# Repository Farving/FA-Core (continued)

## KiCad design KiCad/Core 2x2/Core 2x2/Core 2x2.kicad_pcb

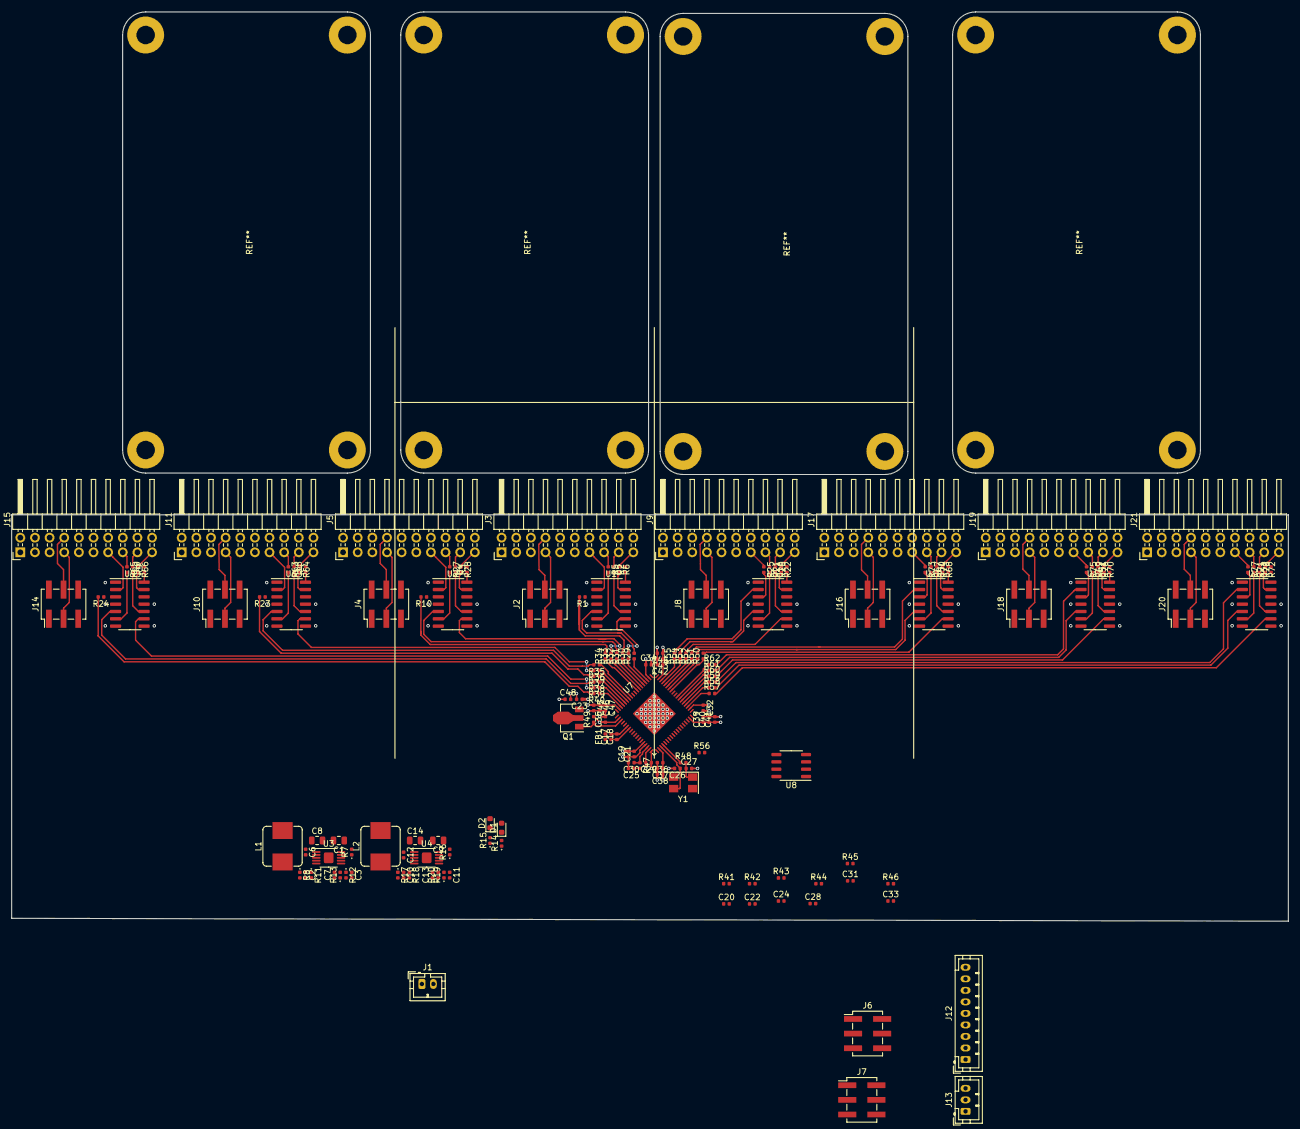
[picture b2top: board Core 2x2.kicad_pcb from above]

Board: 4 copper layers, 221.5 x 70.5 mm, 170 parts (0 on the bottom side), 181 nets.

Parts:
C1, C8, C9, C14: 10u; C_0805_2012Metric
C2, C10, C38, C41, C44, C47: 1u; C_0402_1005Metric
C3, C11, C36, C39, C42, C45: 10n; C_0402_1005Metric
C4, C5, C6, C12, C15, C16, C18, C21, C29, C32, C34, C35, C37, C40, C43, C46, C49, C50, C51, C52: 100n; C_0402_1005Metric
C7, C13: 10p; C_0402_1005Metric
C17, C19, C23, C48: 10u; C_0402_1005Metric
C20, C22, C24, C28, C31, C33: 100p; C_0402_1005Metric
C25: 5.6n; C_0402_1005Metric
C26, C27: 22p; C_0402_1005Metric
C30: 150p; C_0402_1005Metric
D1, D2: LED_Small; D_0603_1608Metric
FB1: 600Z; L_0402_1005Metric
J1: Conn_01x02_Female; JST_PH_B2B-PH-K_1x02_P2.00mm_Vertical
J2, J4, J6, J7, J8, J10, J14, J16, J18, J20: Conn_02x03_Odd_Even; PinHeader_2x03_P2.54mm_Vertical_SMD
J3, J5, J9, J11, J15, J17, J19, J21: 02x10; PinHeader_2x10_P2.54mm_Horizontal
J12: Conn_01x09_Male; JST_PH_B9B-PH-K_1x09_P2.00mm_Vertical
J13: Conn_01x03_Male; JST_PH_B3B-PH-K_1x03_P2.00mm_Vertical
L1, L2: 10u; L_Bourns_SRP7028A_7.3x6.6mm
Q1: 2STF2550; SOT-89-3
R1, R2, R3, R4, R5, R6, R9, R10, R21, R22, R23, R24, R25, R26, R27, R28, R29, R30, R31, R32, R33, R34, R35, R36, R37, R38, R39, R40, R50, R51, R52, R53, R54, R55, R56, R57, R58, R59, R60, R61, R62, R63, R64, R65, R66, R67, R68, R69, R70, R71, R72, R73, R74, R75, R76, R77, R78: 33R; R_0402_1005Metric
R7, R8, R16, R17: 0R; D_0402_1005Metric
R11, R18: 18k; D_0402_1005Metric
R12: 180k; D_0402_1005Metric
R13, R20: 1M; D_0402_1005Metric
R14, R15: 100R; D_0402_1005Metric
R19: 300k; D_0402_1005Metric
R41, R42, R43, R44, R45, R46, R48: 100R; R_0402_1005Metric
R47: 4.32k; R_0402_1005Metric
R49: 1k; R_0402_1005Metric
U1, U2, U5, U6, U9, U10, U11, U12: SN74AHC125; SOIC-14_3.9x8.7mm_P1.27mm
U3, U4: LT8608; MSOP-10-1EP_3x3mm_P0.5mm_EP1.68x1.88mm
U7: ADAU1452; LFCSP-72-1EP_10x10mm_P0.5mm_EP5.3x5.3mm
U8: M95M01; SO-8_3.9x4.9mm_P1.27mm
Y1: 12.288MHz; Crystal_SMD_5032-4Pin_5.0x3.2mm

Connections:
+3V3: C4.1, C5.1, C13.1, C14.1, C15.1, C16.1, C23.1, C29.1, C32.1, C34.1, C35.1, C49.1, C50.1, C51.1, C52.1, FB1.2, J3.1, J5.1, J9.1, J11.1, J15.1, J17.1, J19.1, J21.1, L2.2, Q1.3, R20.1, R49.2, U1.14, U2.14, U5.14, U6.14, U7.2, U7.18, U7.38, U7.56, U9.14, U10.14, U11.14, U12.14
+5V: C7.1, C8.1, C9.1, D1.2, D2.2, J3.2, J5.2, J9.2, J11.2, J15.2, J17.2, J19.2, J21.2, L1.2, R13.1, R16.1, U4.9
/DSP/AVDD: C17.1, C18.1, C19.1, C21.1, C25.2, C30.2, FB1.1, U7.7, U7.15
/DSP/BCLKI0: R29.2, U1.5
/DSP/BCLKI1: R32.2, U2.5
/DSP/BCLKI2: R35.2, U6.5
/DSP/BCLKI3: R38.2, U9.5
/DSP/BCLKO0: R58.2, U12.5
/DSP/BCLKO1: R61.2, U11.5
/DSP/BCLKO2: R51.2, U10.5
/DSP/BCLKO3: R54.2, U5.5
/DSP/DVDD: C36.1, C37.1, C38.1, C39.1, C40.1, C41.1, C42.1, C43.1, C44.1, C45.1, C46.1, C47.1, C48.1, Q1.2, U7.20, U7.35, U7.53, U7.71
/DSP/LRCLKI0: R30.2, U1.9
/DSP/LRCLKI1: R33.2, U2.9
/DSP/LRCLKI2: R36.2, U6.9
/DSP/LRCLKI3: R39.2, U9.9
/DSP/LRCLKO0: R57.2, U12.9
/DSP/LRCLKO1: R60.2, U11.9
/DSP/LRCLKO2: R50.2, U10.9
/DSP/LRCLKO3: R53.2, U5.9
/DSP/SDO0: R59.2, U12.2
/DSP/SDO1: R62.2, U11.2
/DSP/SDO2: R52.2, U10.2
/DSP/SDO3: R55.2, U5.2
/I2C_SCL: J2.1, J4.1, J8.1, J10.1, J13.2, J14.1, J16.1, J18.1, J20.1
/I2C_SDA: J2.2, J4.2, J8.2, J10.2, J13.3, J14.2, J16.2, J18.2, J20.2
/MCLK: R56.2, U1.12, U2.12, U5.12, U6.12, U9.12, U10.12, U11.12, U12.12
/MUTE: J3.6, J5.6, J9.6, J11.6, J15.6, J17.6, J19.6, J21.6
/PG_3V3: R15.1, U4.8
/PG_5V: R14.1, U3.8
/SDI0: R1.2, R31.2
/SDI1: R10.2, R34.2
/SDI2: R23.2, R37.2
/SDI3: R24.2, R40.2
/SHDN: J3.5, J5.5, J9.5, J11.5, J15.5, J17.5, J19.5, J21.5
/SPI_MISO: J3.9, J5.9, J9.9, J11.9, J12.3, J15.9, J17.9, J19.9, J21.9
/SPI_MOSI: J2.6, J4.6, J8.6, J10.6, J12.4, J14.6, J16.6, J18.6, J20.6
/SPI_SCK: J2.5, J4.5, J8.5, J10.5, J12.2, J14.5, J16.5, J18.5, J20.5
/SPI_SS3: J3.10, J5.10, J9.10, J11.10, J12.8, J15.10, J17.10, J19.10, J21.10
GND: C1.2, C2.2, C3.2, C4.2, C5.2, C8.2, C9.2, C10.2, C11.2, C14.2, C15.2, C16.2, C17.2, C18.2, C19.2, C20.2, C21.2, C22.2, C23.2, C24.2, C26.2, C27.2, C28.2, C29.2, C31.2, C32.2, C33.2, C34.2, C35.2, C36.2, C37.2, C38.2, C39.2, C40.2, C41.2, C42.2, C43.2, C44.2, C45.2, C46.2, C47.2, C48.2, C49.2, C50.2, C51.2, C52.2, J1.2, J3.3, J3.4, J3.14, J3.16, J3.18, J3.20, J5.3, J5.4, J5.14, J5.16, J5.18, J5.20, J9.3, J9.4, J9.14, J9.16, J9.18, J9.20, J11.3, J11.4, J11.14, J11.16, J11.18, J11.20, J12.1, J13.1, J15.3, J15.4, J15.14, J15.16, J15.18, J15.20, J17.3, J17.4, J17.14, J17.16, J17.18, J17.20, J19.3, J19.4, J19.14, J19.16, J19.18, J19.20, J21.3, J21.4, J21.14, J21.16, J21.18, J21.20, R11.2, R12.2, R18.2, R19.2, U1.1, U1.4, U1.7, U1.8, U1.11, U2.1, U2.4, U2.7, U2.8, U2.11, U3.11, U4.11, U5.1, U5.4, U5.7, U5.8, U5.11, U6.1, U6.4, U6.7, U6.8, U6.11, U7.1, U7.6, U7.14, U7.17, U7.19, U7.25, U7.36, U7.37, U7.54, U7.55, U7.72, U7.73, U8.4, U9.1, U9.4, U9.7, U9.8, U9.11, U10.1, U10.4, U10.7, U10.8, U10.11, U11.1, U11.4, U11.7, U11.8, U11.11, U12.1, U12.4, U12.7, U12.8, U12.11, Y1.2, Y1.4
unnamed: C2.1, R8.1, U3.3
unnamed: C3.1, U3.7
unnamed: C6.1, U3.1
unnamed: C6.2, L1.1, U3.2
unnamed: C7.2, R12.1, R13.2, U3.6
unnamed: C10.1, R17.1, U4.3
unnamed: C11.1, U4.7
unnamed: C12.1, U4.1
unnamed: C12.2, L2.1, U4.2
unnamed: C13.2, R19.1, R20.2, U4.6
unnamed: C20.1, R41.1, U7.8
unnamed: C22.1, R42.1, U7.9
unnamed: C24.1, R43.1, U7.10
unnamed: C25.1, R47.2
unnamed: C26.1, U7.21, Y1.3
unnamed: C27.1, R48.2, Y1.1
unnamed: C28.1, R44.1, U7.11
unnamed: C30.1, R47.1, U7.16
unnamed: C31.1, R45.1, U7.12
unnamed: C33.1, R46.1, U7.13
unnamed: D1.1, R14.2
unnamed: D2.1, R15.2
unnamed: J2.3, J3.7
unnamed: J2.4, J3.8
unnamed: J3.13, U1.2
unnamed: J3.15, R5.1
unnamed: J3.17, R2.1
unnamed: J3.19, R6.1
unnamed: J4.3, J5.7
unnamed: J4.4, J5.8
unnamed: J5.13, U2.2
unnamed: J5.15, R27.1
unnamed: J5.17, R3.1
unnamed: J5.19, R28.1
unnamed: J8.3, J9.7
unnamed: J8.4, J9.8
unnamed: J9.13, R25.1
unnamed: J9.15, R21.1
unnamed: J9.17, R26.1
unnamed: J9.19, R22.1
unnamed: J10.3, J11.7
unnamed: J10.4, J11.8
unnamed: J11.13, U6.2
unnamed: J11.15, R63.1
unnamed: J11.17, R4.1
unnamed: J11.19, R64.1
unnamed: J14.3, J15.7
unnamed: J14.4, J15.8
unnamed: J15.13, U9.2
unnamed: J15.15, R65.1
unnamed: J15.17, R9.1
unnamed: J15.19, R66.1
unnamed: J16.3, J17.7
unnamed: J16.4, J17.8
unnamed: J17.13, R73.1
unnamed: J17.15, R67.1
unnamed: J17.17, R74.1
unnamed: J17.19, R68.1
unnamed: J18.3, J19.7
unnamed: J18.4, J19.8
unnamed: J19.13, R75.1
unnamed: J19.15, R69.1
unnamed: J19.17, R76.1
unnamed: J19.19, R70.1
unnamed: J20.3, J21.7
unnamed: J20.4, J21.8
unnamed: J21.13, R77.1
unnamed: J21.15, R71.1
unnamed: J21.17, R78.1
unnamed: J21.19, R72.1
unnamed: Q1.1, R49.1, U7.3
unnamed: R1.1, U1.3
unnamed: R2.2, U1.10
unnamed: R3.2, U2.10
unnamed: R4.2, U6.10
unnamed: R5.2, U1.6
unnamed: R6.2, U1.13
unnamed: R7.2, U3.10
unnamed: R8.2, U3.5
unnamed: R9.2, U9.10
unnamed: R10.1, U2.3
unnamed: R11.1, U3.4
unnamed: R16.2, U4.10
unnamed: R17.2, U4.5
unnamed: R18.1, U4.4
unnamed: R21.2, U5.6
unnamed: R22.2, U5.13
unnamed: R23.1, U6.3
unnamed: R24.1, U9.3
unnamed: R25.2, U5.3
unnamed: R26.2, U5.10
unnamed: R27.2, U2.6
unnamed: R28.2, U2.13
unnamed: R29.1, U7.57
unnamed: R30.1, U7.58
unnamed: R31.1, U7.59
unnamed: R32.1, U7.60
unnamed: R33.1, U7.61
unnamed: R34.1, U7.62
unnamed: R35.1, U7.65
unnamed: R36.1, U7.66
unnamed: R37.1, U7.67
unnamed: R38.1, U7.68
unnamed: R39.1, U7.69
unnamed: R40.1, U7.70
unnamed: R48.1, U7.22
unnamed: R50.1, U7.47
unnamed: R51.1, U7.48
unnamed: R52.1, U7.49
unnamed: R53.1, U7.50
unnamed: R54.1, U7.51
unnamed: R55.1, U7.52
unnamed: R56.1, U7.23
unnamed: R57.1, U7.39
unnamed: R58.1, U7.40
unnamed: R59.1, U7.41
unnamed: R60.1, U7.42
unnamed: R61.1, U7.43
unnamed: R62.1, U7.44
unnamed: R63.2, U6.6
unnamed: R64.2, U6.13
unnamed: R65.2, U9.6
unnamed: R66.2, U9.13
unnamed: R67.2, U10.6
unnamed: R68.2, U10.13
unnamed: R69.2, U11.6
unnamed: R70.2, U11.13
unnamed: R71.2, U12.6
unnamed: R72.2, U12.13
unnamed: R73.2, U10.3
unnamed: R74.2, U10.10
unnamed: R75.2, U11.3
unnamed: R76.2, U11.10
unnamed: R77.2, U12.3
unnamed: R78.2, U12.10
unnamed: U7.26, U8.1
unnamed: U7.27, U8.5
unnamed: U7.28, U8.6
unnamed: U7.29, U8.2
unnamed: U8.3, U8.7
VDD: C1.1, J1.1, R7.1, U3.9, U8.8

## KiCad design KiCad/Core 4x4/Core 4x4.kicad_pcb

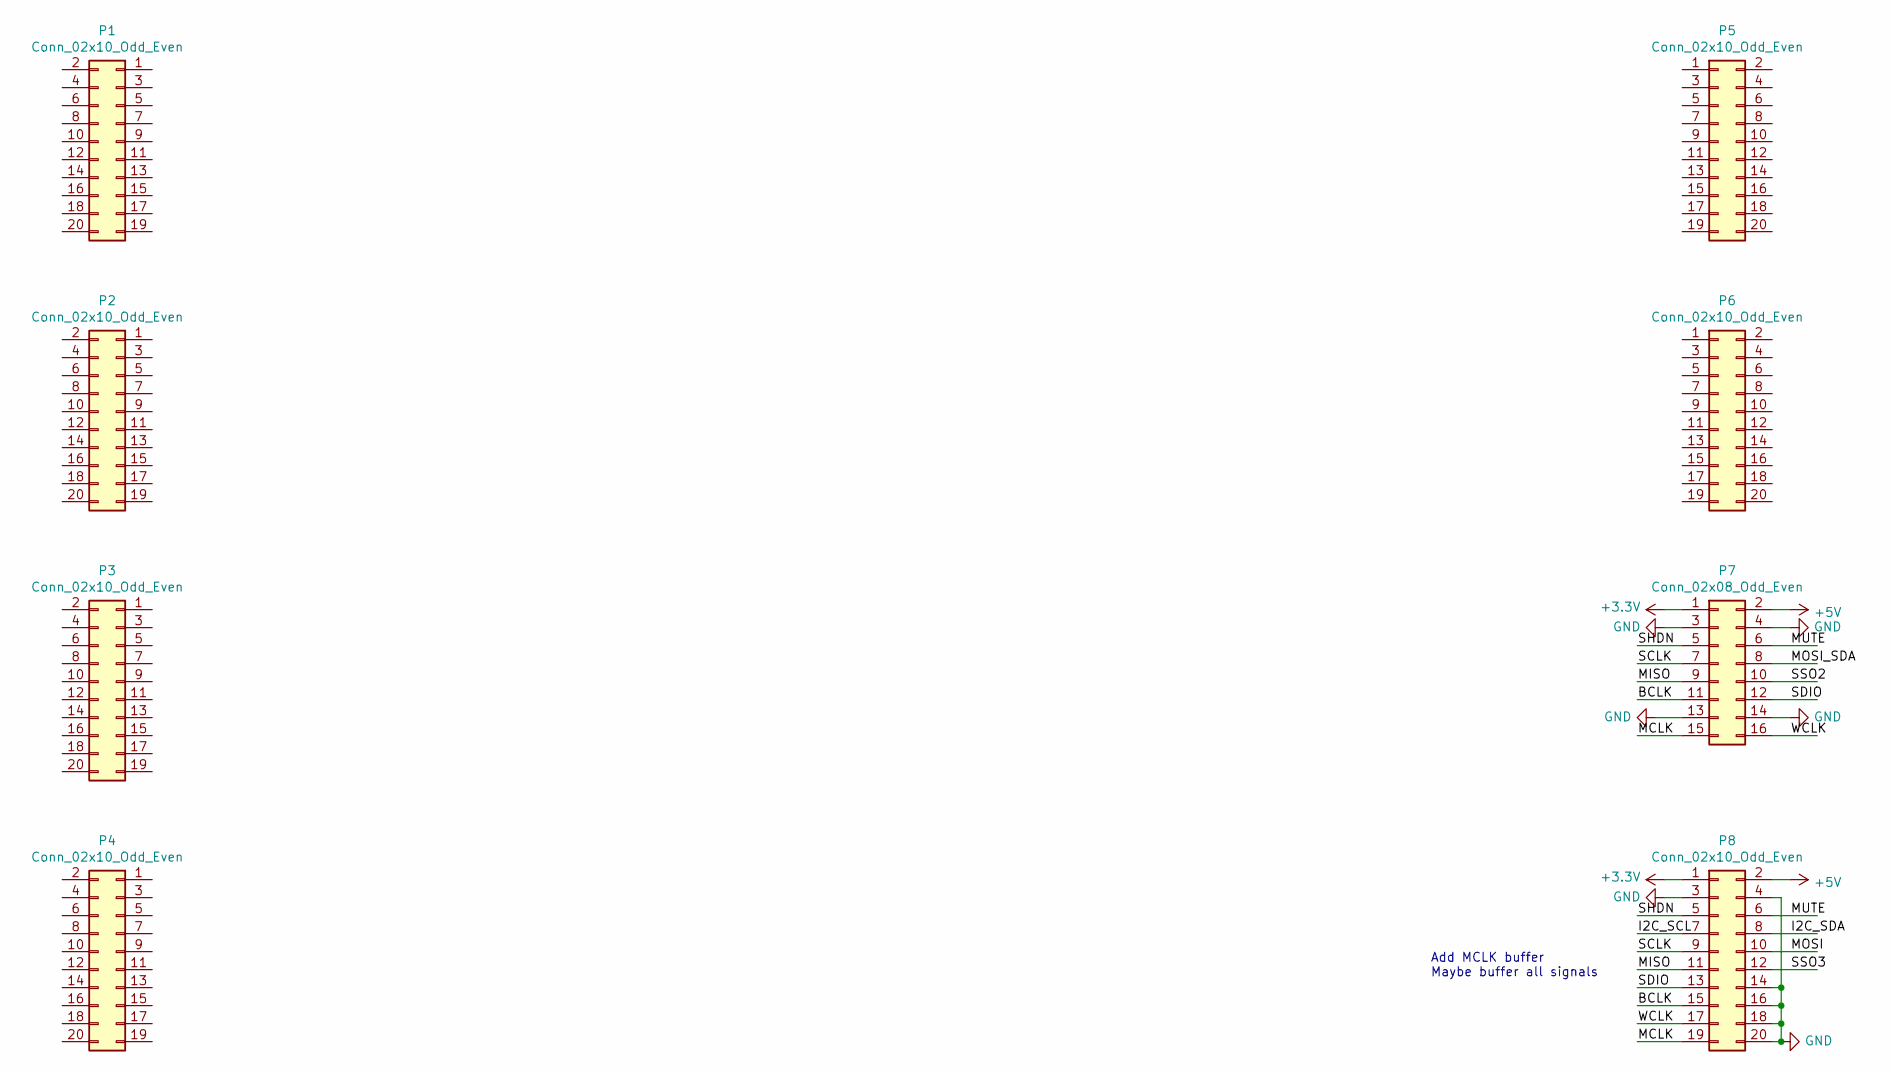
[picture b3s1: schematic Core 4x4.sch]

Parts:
P1, P2, P3, P4, P5, P6, P8: Conn_02x10_Odd_Even; PinSocket_2x10_P2.54mm_Horizontal
P7: Conn_02x08_Odd_Even; PinSocket_2x08_P2.54mm_Horizontal

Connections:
+3V3: P7.1, P8.1
+5V: P7.2, P8.2
/BCLK: P7.11, P8.15
/I2C_SCL: P8.7
/I2C_SDA: P8.8
/MCLK: P7.15, P8.19
/MISO: P7.9, P8.11
/MOSI: P8.10
/MOSI_SDA: P7.8
/MUTE: P7.6, P8.6
/SCLK: P7.7, P8.9
/SDIO: P7.12, P8.13
/SHDN: P7.5, P8.5
/SSO2: P7.10
/SSO3: P8.12
/WCLK: P7.16, P8.17
GND: P7.3, P7.4, P7.13, P7.14, P8.3, P8.4, P8.14, P8.16, P8.18, P8.20

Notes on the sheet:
Add MCLK buffer Maybe buffer all signals

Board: 4 copper layers, 8 parts (0 on the bottom side), 11 nets, no tracks yet.

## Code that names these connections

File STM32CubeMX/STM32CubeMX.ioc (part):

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Mcu.Name=STM32F042G(4-6)Ux
Mcu.Package=UFQFPN28
Mcu.UserName=STM32F042G4Ux
PA0.GPIOParameters=GPIO_Label,GPIO_ModeDefaultOutputPP
PA0.GPIO_Label=SHDN
PA0.GPIO_ModeDefaultOutputPP=GPIO_MODE_OUTPUT_OD
PA0.Signal=GPIO_Output
PA1.GPIOParameters=GPIO_Label,GPIO_ModeDefaultOutputPP
PA1.GPIO_Label=MUTE
PA1.GPIO_ModeDefaultOutputPP=GPIO_MODE_OUTPUT_OD
PA1.Signal=GPIO_Output
PA11.Mode=Device
PA11.Signal=USB_DM
PA12.Mode=Device
PA12.Signal=USB_DP
PA13.Mode=Serial_Wire
PA13.Signal=SYS_SWDIO
PA14.Mode=Serial_Wire
PA14.Signal=SYS_SWCLK
PA15.Mode=NSS_Signal_Hard_Output
PA15.Signal=SPI1_NSS
PA2.GPIOParameters=GPIO_Label
PA2.GPIO_Label=ADAU1452_SELFBOOT
PA2.Signal=GPIO_Output
PB3.Mode=Full_Duplex_Master
PB3.Signal=SPI1_SCK
PB4.Mode=Full_Duplex_Master
PB4.Signal=SPI1_MISO
PB5.Mode=Full_Duplex_Master
PB5.Signal=SPI1_MOSI
PB6.GPIOParameters=GPIO_Label
PB6.GPIO_Label=USBi_DET
PB6.Signal=GPXTI6
PB7.GPIOParameters=GPIO_PuPd,GPIO_Label,GPIO_ModeDefaultOutputPP
PB7.GPIO_Label=ADAU1452_nRESET
PB7.GPIO_ModeDefaultOutputPP=GPIO_MODE_OUTPUT_OD
PB7.GPIO_PuPd=GPIO_NOPULL
PB7.Signal=GPIO_Output
PB8.GPIOParameters=GPIO_Label
PB8.GPIO_Label=BOOT0
PB8.Signal=GPIO_Input
PF0-OSC_IN.Mode=I2C
PF0-OSC_IN.Signal=I2C1_SDA
PF1-OSC_OUT.Mode=I2C
PF1-OSC_OUT.Signal=I2C1_SCL
RCC.SYSCLKFreq_VALUE=48000000
RCC.SYSCLKSource=RCC_SYSCLKSOURCE_HSI48
board=custom

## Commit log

2020-03-25 Add ADAU1452 Schematic
2020-03-25 Init Core 4x4 Project
2020-03-25 Init Core 2x2 Project
2020-06-30 Progress Commit
2020-11-16 Add STM32Cube project
2020-11-16 Add Mute-logic simulation
2020-11-16 Add new PSU
2020-11-16 Pre-release commit
